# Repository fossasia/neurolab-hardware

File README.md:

# Neurolab Hardware

Repository for Neurolab Open Hardware platform.

We are developing a neuro-device to collect brainwaves as a headband with integrated electronics. This repository holds the PCB schematics and layouts for the Neurolab Hardware. 

Front Side               | Back Side
 ----------------------- | ---------------------------
 | 

## Buy

* You can get the device in future from the [FOSSASIA Shop](https://fossasia.com).
* More resellers will be listed on the [PSLab website](https://pslab.io/shop/).

## Communication

* The Neurolab [chat channel is on Gitter](https://gitter.im/fossasia/neurolab).
* Please also join us on the [Mailing List](https://groups.google.com/forum/#!forum/pslab-fossasia).

## Goal and Roadmap
The goal of the Neurolab project is to develop an easy to use open hardware measurement headset device for brain waves that can be plugged into an Android smartphone and a software application and enables us to understand our brains better.

Our brains communicate through neurotransmitters and their activity emits electricity. The neuroheadset measures that electricity on the skin of the forehead and the software processes the signal so that it can translated into a visual or auditory representation. The data that can be collected can be analysed to identify mental health, stress, relaxation and even diseases like Alzheimer. 

Current devices in the medical industry are usually not accessible by doctors due to their high pricing. They are also complicated to use. The idea of the device is to integrate it into a headband and focus on signals that can be obtained through the frontal lobe.

A difference to existing projects like OpenBCI is that it will not be necessary to 3D print large headsets. Instead we are focusing on creating a device that collects as much data as possible through the forehead. To achieve this goal we are using high-grade sensors and flexible electronics.

## License

This project is licensed under the Apache License 2.0. A copy of [LICENSE](LICENSE) is to be present along with the source code. To obtain the software under a different license, please contact FOSSASIA.

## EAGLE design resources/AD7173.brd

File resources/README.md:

# fossasia-neurofox
PCB schematics and layouts for NeuroFox

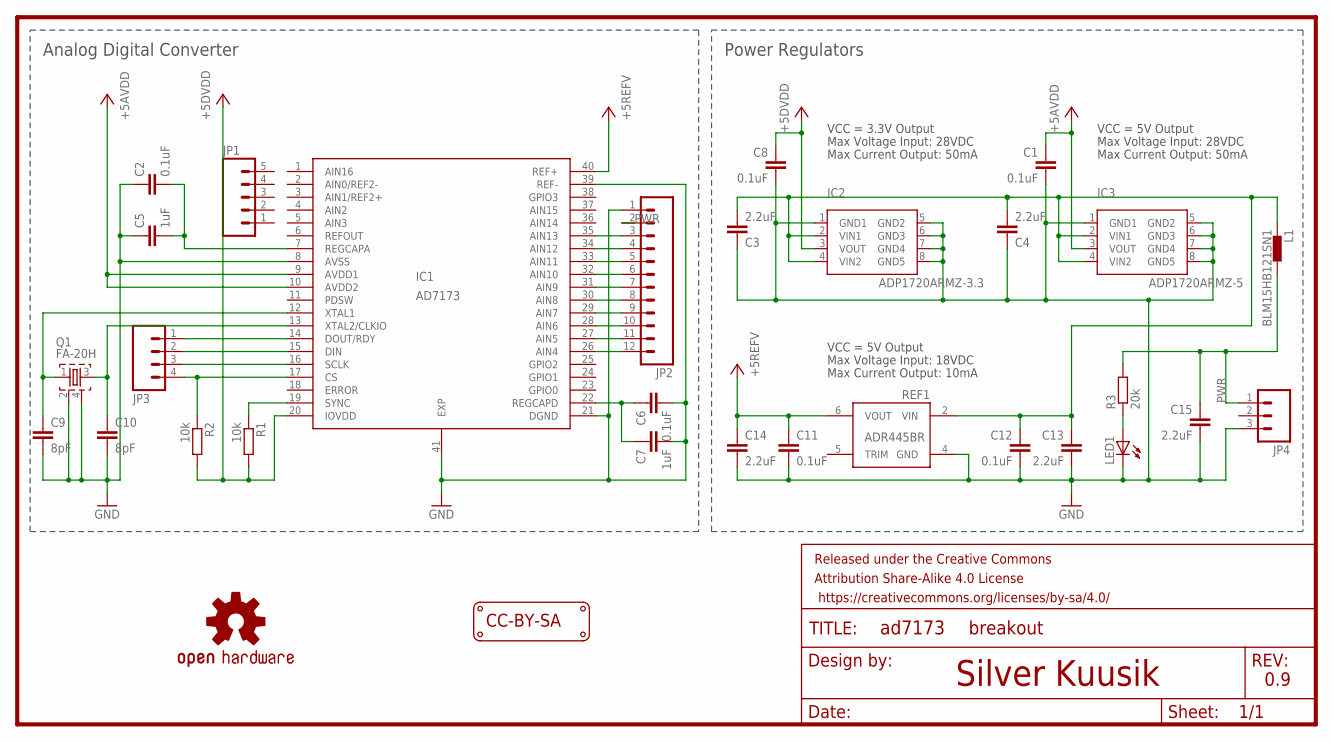
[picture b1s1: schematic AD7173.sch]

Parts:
C1, C2, C6, C8, C11, C12: 0.1uF; C0402
C3, C4, C13, C14, C15: 2.2uF; C0402
C5, C7: 1uF; C0402
C9, C10: 8pF; C0402
FRAME1: FRAME-LETTER; CREATIVE_COMMONS
IC1: AD7173; LFCSP_WQ6X6MM
IC2: ADP1720ARMZ-3.3; MSOP08
IC3: ADP1720ARMZ-5; MSOP08
JP1: M05PTH; 1X05
JP2: M12PTH; 1X12
JP3: M04PTH; 1X04
JP4: M03PTH; 1X03
L1: BLM15HB121SN1; 0402
LED1: LEDCHIP-LED0603; CHIP-LED0603
LOGO1: OSHW-LOGOS; OSHW-LOGO-S
LOGO2: LOGO_CC-BY-SA
Q1: FA-20H
R1, R2: 10k; R0402
R3: 20k; R0402
REF1: ADR445BR; SO8

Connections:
+3V3: C8.1, IC1.20 (IOVDD), IC2.3 (VOUT), R1.2, R2.2
+5V: C1.1, IC1.9 (AVDD1), IC1.10 (AVDD2), IC3.3 (VOUT)
GND: C1.2, C2.1, C3.1, C4.1, C5.1, C6.2, C7.2, C8.2, C9.2, C10.2, C11.2, C12.2, C13.2, C14.2, C15.2, IC1.8 (AVSS), IC1.21 (DGND), IC1.39 (REF-), IC1.41 (EXP), IC2.1 (GND1), IC2.5 (GND2), IC2.6 (GND3), IC2.7 (GND4), IC2.8 (GND5), IC3.1 (GND1), IC3.5 (GND2), IC3.6 (GND3), IC3.7 (GND4), IC3.8 (GND5), JP2.1, JP4.3, LED1.C, Q1.2, Q1.4, REF1.4 (GND)
unnamed: IC1.16 (SCLK), JP3.3
unnamed: IC1.17 (CS), JP3.4, R2.1
unnamed: C6.1, C7.1, IC1.22 (REGCAPD)
unnamed: IC1.34 (AIN12), JP2.4
unnamed: C2.2, C5.2, IC1.7 (REGCAPA)
unnamed: IC1.35 (AIN13), JP2.3
unnamed: IC1.33 (AIN11), JP2.5
unnamed: IC1.32 (AIN10), JP2.6
unnamed: IC1.31 (AIN9), JP2.7
unnamed: IC1.30 (AIN8), JP2.8
unnamed: IC1.29 (AIN7), JP2.9
unnamed: IC1.15 (DIN), JP3.2
unnamed: IC1.27 (AIN5), JP2.11
unnamed: IC1.26 (AIN4), JP2.12
unnamed: C10.1, IC1.13 (XTAL2/CLKIO), Q1.3
unnamed: IC1.28 (AIN6), JP2.10
unnamed: IC1.14 (DOUT/RDY), JP3.1
unnamed: C9.1, IC1.12 (XTAL1), Q1.1
unnamed: LED1.A, R3.1
unnamed: IC1.19 (SYNC), R1.1
PWR: C15.1, JP2.2, JP4.1, L1.2, R3.2
VCC: C11.1, C14.1, IC1.40 (REF+), REF1.6 (VOUT)
VIN: C3.2, C4.2, C12.1, C13.1, IC2.2 (VIN1), IC2.4 (VIN2), IC3.2 (VIN1), IC3.4 (VIN2), L1.1, REF1.2 (VIN)

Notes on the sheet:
Power Regulators
Analog Digital Converter
VCC = 3.3V Output
Max Current Output: 50mA
Max Voltage Input: 28VDC
VCC = 5V Output
Max Voltage Input: 18VDC
Max Current Output: 10mA
Silver Kuusik
breakout
0.9

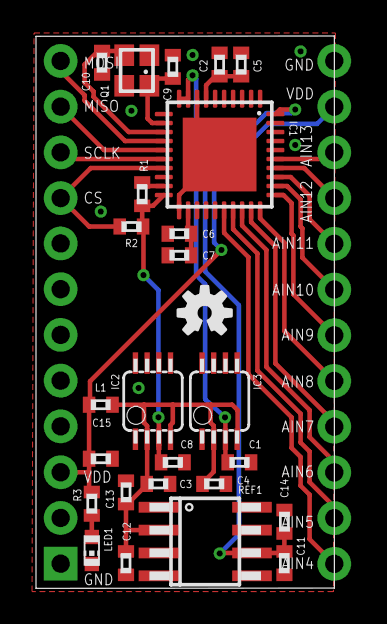
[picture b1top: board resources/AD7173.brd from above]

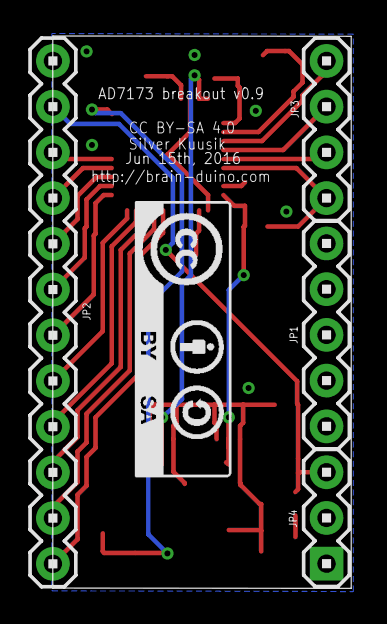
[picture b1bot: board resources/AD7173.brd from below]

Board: 2 copper layers, 16.6 x 30.7 mm, 32 parts (5 on the bottom side), 26 nets.

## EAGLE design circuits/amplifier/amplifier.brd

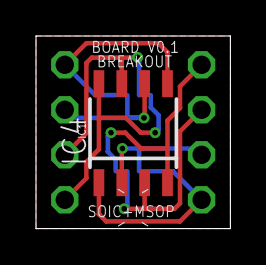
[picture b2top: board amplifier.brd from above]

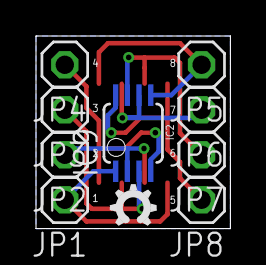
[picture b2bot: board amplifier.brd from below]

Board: 2 copper layers, 10.8 x 10.7 mm, 10 parts (9 on the bottom side), 8 nets.

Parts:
IC4: OPA2134D; SOIC8
IC9: MSOP08
JP1, JP2, JP3, JP4, JP5, JP6, JP7, JP8: 1X01

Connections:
unnamed: IC4.1, IC9.1, JP1.1
unnamed: IC4.6, IC9.6, JP6.1
unnamed: IC4.7, IC9.7, JP7.1
unnamed: IC4.8, IC9.8, JP8.1
unnamed: IC4.2, IC9.2, JP2.1
unnamed: IC4.3, IC9.3, JP3.1
unnamed: IC4.4, IC9.4, JP4.1
unnamed: IC4.5, IC9.5, JP5.1

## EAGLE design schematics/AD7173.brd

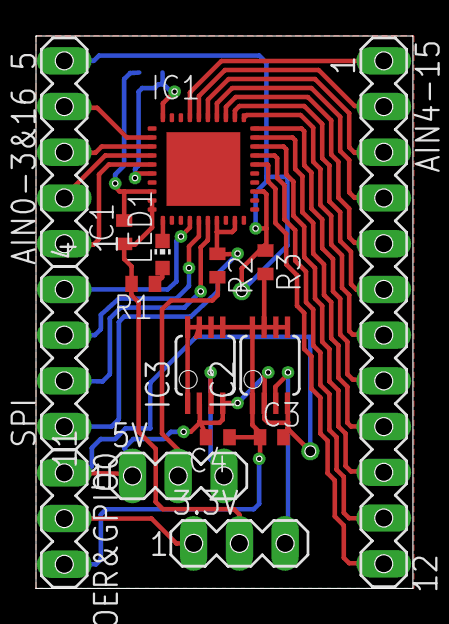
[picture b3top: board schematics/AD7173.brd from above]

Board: 2 copper layers, 20.9 x 30.7 mm, 17 parts (1 on the bottom side), 29 nets.

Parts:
3.3V, 5V: MA03-1
AIN0-3&16: MA05-1
AIN4-15: MA12-1
C1, C2, C3, C4: 0.1uF; C0402
IC1: AD7173; LFCSP_WQ6X6MM
IC2, IC3: LM3485; MSOP08
LED1: CHIP-LED0603
PWOER&GPIO0: MA03-1
R1, R2, R3: 10k; R0402
SPI: MA04-1

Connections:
+3V3: 5V.2, R2.2
+5V: 3.3V.2, C1.1, IC1.9, IC1.10, R1.2
GND: C1.2, C2.1, C3.1, C4.1, IC1.8, IC2.1, IC2.5, IC2.6, IC2.7, IC2.8, IC3.1, IC3.5, IC3.6, IC3.7, IC3.8, PWOER&GPIO0.3, R3.2
unnamed: LED1.A, R1.1
unnamed: IC1.17, IC1.19, R2.1, SPI.1
unnamed: AIN4-15.1, IC1.37
unnamed: AIN0-3&16.5, IC1.23, R3.1
unnamed: C2.2, IC1.6, IC1.40
unnamed: AIN4-15.2, IC1.36
unnamed: AIN4-15.3, IC1.35
unnamed: AIN4-15.4, IC1.34
unnamed: AIN4-15.5, IC1.33
unnamed: AIN4-15.6, IC1.32
unnamed: AIN4-15.7, IC1.31
unnamed: AIN4-15.8, IC1.30
unnamed: AIN4-15.9, IC1.29
unnamed: AIN4-15.10, IC1.28
unnamed: AIN4-15.11, IC1.27
unnamed: AIN4-15.12, IC1.26
unnamed: AIN0-3&16.1, IC1.5
unnamed: AIN0-3&16.2, IC1.4
unnamed: AIN0-3&16.3, IC1.3
unnamed: AIN0-3&16.4, IC1.2
unnamed: 3.3V.1, PWOER&GPIO0.2
unnamed: IC1.14, SPI.4
unnamed: IC1.15, SPI.3
unnamed: IC1.16, SPI.2
unnamed: 5V.1, C3.2, C4.2, IC2.2, IC2.4, IC3.2, IC3.4, PWOER&GPIO0.1
SPI: IC1.11, LED1.C

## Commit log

2014-04-26 AD7173-8.py added debug messages
2014-04-26 AD7173-8.ino refactoring + read and write registers
2014-04-26 AD7173-8.py added 1 - 3 bit debugging functions
2014-04-26 AD7173-8.ino added register defines, updated debugging
2014-04-29 AD7173-8.ino added speed and conversion mode functions
2014-04-29 AD7173-8.py updated offset binary calculation
2014-04-29 bipolar.ino removed obsolete
2014-04-30 Update AD7173-8.ino
    updated chip illustration
2014-05-03 AD7173-8.ino added channel enable/disable function
2014-05-03 AD7173-8.ino updated speed, mode and channel functions
2014-05-03 AD7173-8.ino fixed enable_adc_channel
2014-05-04 AD7173-8.ino improved debuging
2014-05-06 AD7173-8.ino updated adc_data_mode
2014-05-06 AD7173-8.ino fixed adc_data_mode
2014-05-13 AD7173-*.* renamed files
2014-05-13 AD7173.lbr added eagle library
2014-05-13 AD7173.py renamed file
2014-05-13 AD7173.pdf renamed file
2014-05-13 AD7173.ino refactor + added setup coding output
2014-05-13 README.md update
2014-05-13 AD7173.ino added get current adc data channel
2014-05-17 schematics/* added eagle schematics files for the ADC
2014-05-22 schematics/AD7173.lbr updated AD7173 eagle library
2014-05-22 AD7173.ino fixed enable_adc_channel AINs
2014-05-22 AD7173/* create arduino library, renamed schematics
2014-05-22 AD7173.ino removed obsolete file
2014-05-24 AD7173/AD7173.* contructor for default values
2014-05-26 AD7173/keywords.txt updated keywords
2014-05-26 AD7173/examples/Basic/Basic.ino udated basic example
2014-05-26 AD7173/AD7173.cpp/.h refactor + fixed enabling channels
2014-06-12 datasheets/ added datasheets folder
2014-06-12 circuits/* updated eagle circuits
2014-06-12 AD7173.pdf removed obsolete file
2014-07-02 AD7173/AD7173.cpp fixed enable_channel ain1
2014-07-02 AD7173.* added enable_filter_enhancement
2014-07-26 circuits/AD7173/* moved AD7173 circuit to it's own folder
2014-07-26 circuits/amplifier/* added amplifier circuit
2015-03-18 updated aplifier circuit
2015-03-18 updated gitignore
2015-04-11 added ADC test code for raspberry pi
2015-04-11 upadted AD7173 circuits
2015-04-11 upadted raspberry pi code
2015-06-27 added adr44X datasheet
2015-06-27 updated AD7173 circuit
2015-06-28 added ferrite bean datasheet
2015-06-28 updated AD7173 breakout board
2015-07-03 upadted AD7173 breakout board
2015-07-04 updated git ignore
2015-07-29 added set_clock_mode
2015-07-29 folder restructure
2015-08-19 refactoring code, enhanced debug
2015-08-20 changed coding mode func name
2015-08-20 updated raspberry pi library
2015-08-24 renamed files
2015-08-24 refactoring
2015-08-24 added sending data over bluetooth
2015-09-03 made pads longer
2015-09-03 updated pins, components placing
2015-09-05 small margin updates
2015-09-05 updated ignore
2015-09-05 updated label
2016-01-11 Update LICENSE
    changed to CC BY SA
2016-01-11 Added instructions for adding tasks
2016-01-11 Included corresponding task
2016-01-11 Added approved task
2016-01-11 Add Node.js GitHub OAuth
2016-01-11 Light out:javascript Task uploaded.
2016-01-11 Added my tasks for GCI
2016-01-12 Create Index.html
    Index file for the lights out task. Standalone
2016-01-12 Added the Index.html for Google CGI
2016-01-12 Revert "Added the Index.html for Google CGI"
    This reverts commit 200c518c136bad4b05d299c9e74db4a0a3626aa3.
2016-01-12 Improved website.
2016-01-12 Updated my task for Google CGI
2016-01-12 The screenshots
    Whoops, looks like I forgot to add them in the first shot
2016-01-12 Update LICENSE
    can't change license now, changed it back ^_^
2016-01-13 Fix preview links
2016-01-13 My project
2016-01-14 typo
2016-01-15 Added my task code
2016-01-15 Added Tweets_Retriver task -Yathannsh
2016-01-17 Added my file
2016-01-19 My Task Files
2016-01-19 Update AD7173.cpp
    fix: enable_channel, value wrongly shifted
2016-01-19 geolocation
2016-01-20 Get geolocation by Lee Wei Jie
2016-01-20 Improve design and UI and display message if user rejects location request
2016-01-23 Added my projects
2016-01-23 Add [Hangman]_[Sawyer_Charles]
2016-01-24 Added all my Projects
2016-01-25 added hangman
2016-02-11 Added my projects!
2016-05-19 Update AD7173.cpp
    fixed set_clock_mode
2018-11-13 init: updated repo with new layouts
2018-11-14 refactor: reordered folder structure
2018-11-17 updated schematics
2018-11-18 added ADC Chip
2018-11-20 added arduino base
2018-11-21 added footprints
2018-11-21 complete schematics
2018-11-21 added decouple capacitors
2018-11-24 pcb layout for amplifier block
2018-11-24 feat: power circuitry
2018-11-26 feat: attenuator and clock circuits
2018-11-27 feat: filter circuits
    refactor
2018-11-28 feat: ADC Circuit
2018-11-29 refactor: route improvements
2018-11-29 docs: updated readme
    typo
2018-11-29 docs: added BoM
2018-12-01 optimize: routing and placement
    optimize: squeeze space
    optimize: squeeze space contd.
    optimize: contd.
2018-12-03 optimize: component placement
2018-12-03 optimize: reduce spacing 20mils
2018-12-03 optimize: redundant foot prints
2018-12-03 optimize: routing to minimize length
2018-12-03 optimize: alternative route for +5V
2018-12-03 optimize: route parts
2018-12-03 optimize: removed redundant SPI connector
2018-12-03 optimize: routing SPI
2018-12-04 optimize: final routing
2019-03-26 feat: schematics and readme update
2020-03-27 Update LICENSE
2021-05-22 chore: updated gitignore file
2021-05-22 chore: updated gitignore file (#63)
2021-06-02 Optimized Routing and Fixed DRC

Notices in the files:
resources/AD7173.brd:
CC BY-SA 4.0
parts and their libraries:
SparkFun-Aesthetics: Licensing: Creative Commons ShareAlike 4.0 International - https://creativecommons.org/licenses/by-sa/4.0
SparkFun-Aesthetics: Released under the Creative Commons Attribution Share-Alike 4.0 License
SparkFun-Aesthetics: https://creativecommons.org/licenses/by-sa/4.0
